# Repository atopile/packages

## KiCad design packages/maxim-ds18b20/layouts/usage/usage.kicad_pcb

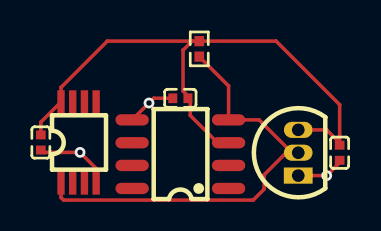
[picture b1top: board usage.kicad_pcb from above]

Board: 2 copper layers, 7 parts (0 on the bottom side), 3 nets.

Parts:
C1, C2, C3: [capacitance: unknown]; C0402
R1: [resistance: unknown]; R0402
U1: SOP-8_L3.0-W3.0-P0.65-LS4.9-BL
U2: SOP-8_L4.9-W3.9-P1.27-LS6.0-BL
U3: TO-92-3_L4.9-W3.7-P1.27-L

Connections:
DQ: R1.1, U1.1, U2.4, U3.2
hv: C1.1, C2.1, C3.1, R1.2, U1.8, U2.3, U3.3
lv: C1.2, C2.2, C3.2, U1.4, U2.5, U3.1

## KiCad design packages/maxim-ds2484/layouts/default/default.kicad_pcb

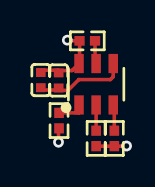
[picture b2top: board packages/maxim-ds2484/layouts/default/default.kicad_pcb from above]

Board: 2 copper layers, 7 parts (0 on the bottom side), 6 nets.

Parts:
C1: 1e-06F; C0402
C2: 1F; C0402
R1, R2, R4: 10000Ω; R0402
R3: 2000Ω; R0402
U1: SOT-23-6_L2.9-W1.6-P0.95-LS2.8-BL

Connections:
IO: R3.2, U1.5
SCL: R1.2, U1.3
SDA: R2.2, U1.2
SLPZ: R4.2, U1.1
hv: C1.1, C2.1, R1.1, R2.1, R3.1, R4.1, U1.6
lv: C1.2, C2.2, U1.4

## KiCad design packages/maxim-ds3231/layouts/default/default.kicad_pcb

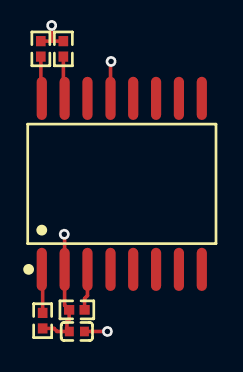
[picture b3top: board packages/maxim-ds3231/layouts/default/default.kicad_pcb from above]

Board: 2 copper layers, 6 parts (0 on the bottom side), 6 nets.

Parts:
C1: 1F; C0402
R1, R2, R3, R4: 10000Ω; R0402
U1: SOIC-16_L10.3-W7.5-P1.27-LS10.3-BL

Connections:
INTSQW: R4.2, U1.3
P32kHz: R1.2, U1.1
SCL: R2.2, U1.16
SDA: R3.2, U1.15
lv: C1.2, U1.13
power-hv: C1.1, R1.1, R2.1, R3.1, R4.1, U1.2

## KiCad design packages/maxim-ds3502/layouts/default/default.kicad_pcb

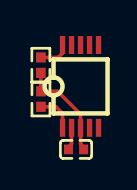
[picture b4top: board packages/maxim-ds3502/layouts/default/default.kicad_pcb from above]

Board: 2 copper layers, 4 parts (0 on the bottom side), 4 nets.

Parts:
C1: 1F; C0402
R1, R2: 4700Ω; R0402
U1: UMAX-10_L3.0-W3.0-P0.50-LS4.9-BL

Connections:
SCL: R1.1, U1.10
SDA: R2.1, U1.1
lv: C1.2, U1.2, U1.4, U1.5
power-hv: C1.1, R1.2, R2.2, U1.3
